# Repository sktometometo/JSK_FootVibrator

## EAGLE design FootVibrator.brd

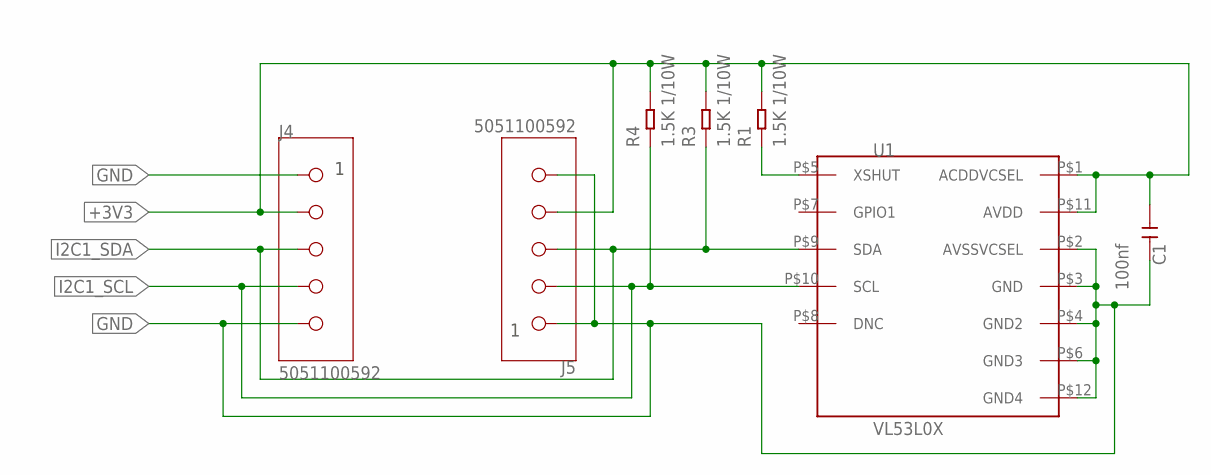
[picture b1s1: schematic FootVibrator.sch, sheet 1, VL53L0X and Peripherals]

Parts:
C1: 100nf; C0603
J4, J5: 5051100592
R1, R3, R4: 1.5K 1/10W; R0603
U1: VL53L0X

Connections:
+3V3: C1.1, J4.2, J5.4, R1.2, R3.2, R4.2, U1.P$1 (ACDDVCSEL), U1.P$11 (AVDD); also elsewhere on the board
GND: C1.2, J4.1, J4.5, J5.1, J5.5, U1.P$2 (AVSSVCSEL), U1.P$3 (GND), U1.P$4 (GND2), U1.P$6 (GND3), U1.P$12 (GND4); also elsewhere on the board
I2C1_SCL: J4.4, J5.2, R4.1, U1.P$10 (SCL); also elsewhere on the board
I2C1_SDA: J4.3, J5.3, R3.1, U1.P$9 (SDA); also elsewhere on the board
VL_XSHUT: R1.1, U1.P$5 (XSHUT)

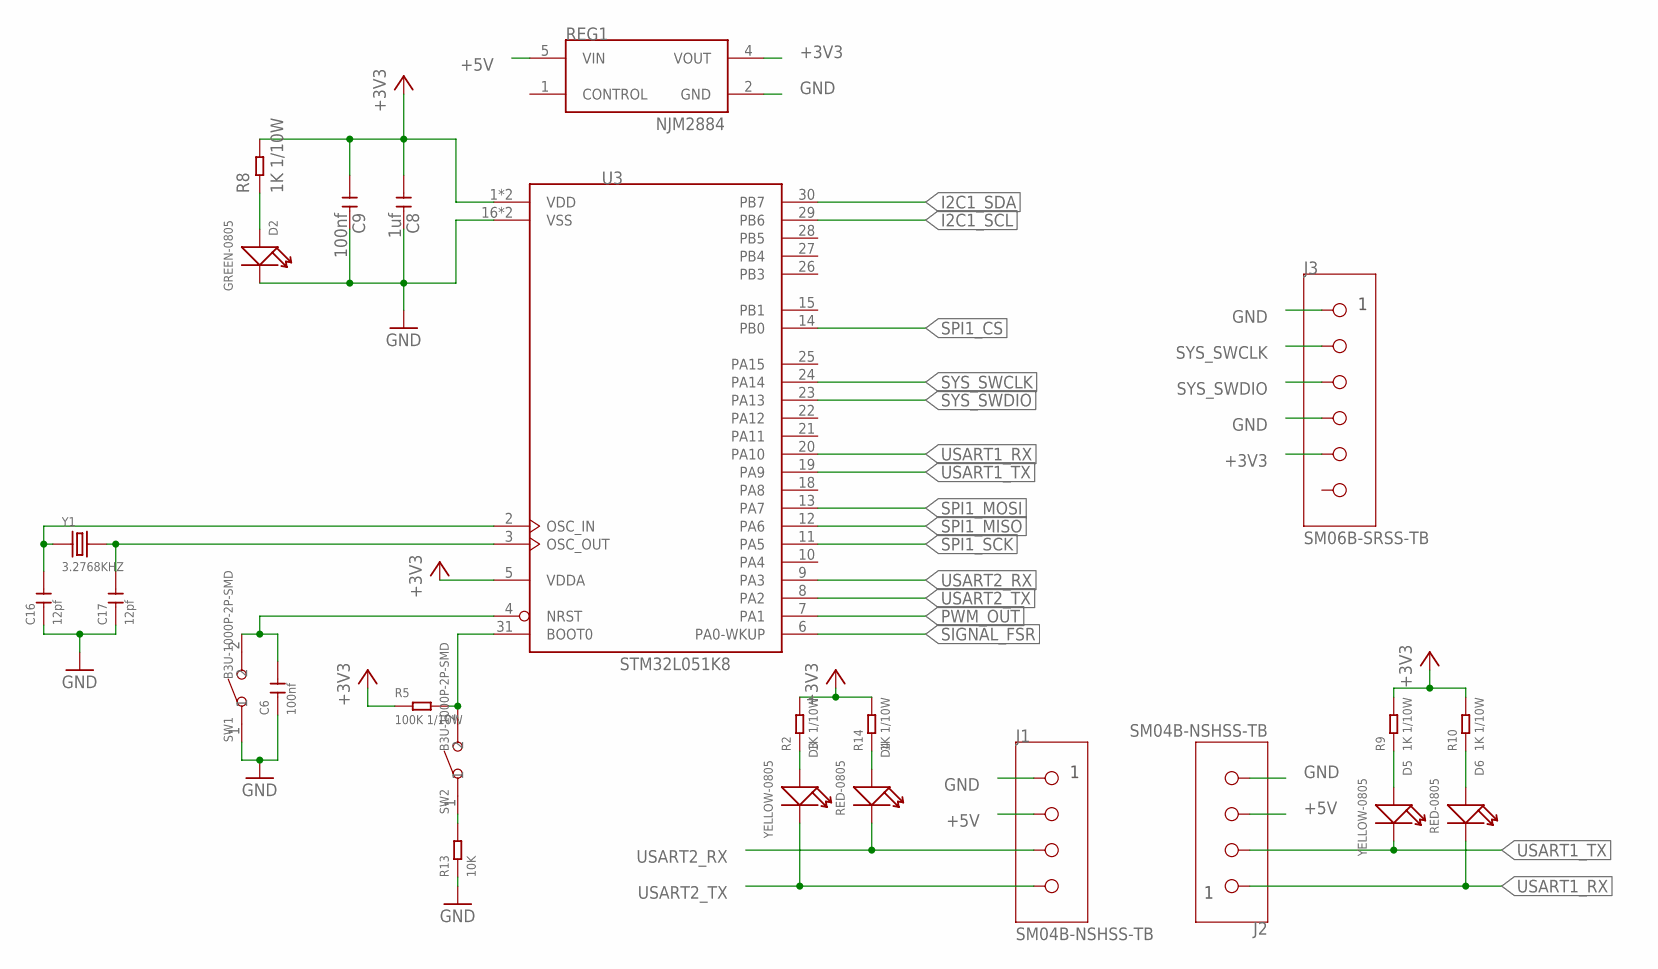
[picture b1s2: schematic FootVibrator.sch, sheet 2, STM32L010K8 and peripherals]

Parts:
C6, C9: 100nf; C0603
C8: 1uf; C0603
C16, C17: 12pf; C0603
D2: GREEN-0805; LED-0805
D3, D5: YELLOW-0805; LED-0805
D4, D6: RED-0805; LED-0805
J1, J2: SM04B-NSHSS-TB
J3: SM06B-SRSS-TB
R2, R8, R9, R10, R14: 1K 1/10W; R0603
R5: 100K 1/10W; R0603
R13: 10K; R0603
REG1: NJM2884; NJM2884-SOT-89-5
SW1, SW2: B3U-1000P-2P-SMD; SW2-2.6-3.0X2.5X1.2+0.4MM
U3: STM32L051K8; LQFP32
Y1: 3.2768KHZ; X2-SMD-L2.0X1.2X0.55MM

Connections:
+3V3: C8.1, C9.1, J3.5, R2.2, R5.1, R8.2, R9.2, R10.2, R14.2, REG1.4 (VOUT), U3.1 (VDD), U3.5 (VDDA), U3.17 (VDD); also elsewhere on the board
+5V: J1.P$2 (2), J2.P$3 (3), REG1.5 (VIN)
GND: C6.1, C8.2, C9.2, C16.1, C17.1, D2.-, J1.P$1 (1), J2.P$4 (4), J3.1, J3.4, R13.1, REG1.2 (GND), SW1.1, U3.16 (VSS), U3.32 (VSS); also elsewhere on the board
I2C1_SCL: U3.29 (PB6); also elsewhere on the board
I2C1_SDA: U3.30 (PB7); also elsewhere on the board
unnamed: R5.2, SW2.2, U3.31 (BOOT0)
unnamed: D3.+, R2.1
unnamed: R13.2, SW2.1
unnamed: D5.+, R9.1
unnamed: D6.+, R10.1
unnamed: D2.+, R8.1
unnamed: C6.2, SW1.2, U3.4 (NRST)
unnamed: D4.+, R14.1
OCC_IN: C16.2, U3.2 (OSC_IN), Y1.1
OCC_OUT: C17.2, U3.3 (OSC_OUT), Y1.2
PWM_OUT: U3.7 (PA1); also elsewhere on the board
SIGNAL_FSR: U3.6 (PA0-WKUP); also elsewhere on the board
SPI1_CS: U3.14 (PB0); also elsewhere on the board
SPI1_MISO: U3.12 (PA6); also elsewhere on the board
SPI1_MOSI: U3.13 (PA7); also elsewhere on the board
SPI1_SCK: U3.11 (PA5); also elsewhere on the board
SYS_SWCLK: J3.2, U3.24 (PA14)
SYS_SWDIO: J3.3, U3.23 (PA13)
USART1_RX: D6.-, J2.P$1 (1), U3.20 (PA10)
USART1_TX: D5.-, J2.P$2 (2), U3.19 (PA9)
USART2_RX: D4.-, J1.P$3 (3), U3.9 (PA3)
USART2_TX: D3.-, J1.P$4 (4), U3.8 (PA2)

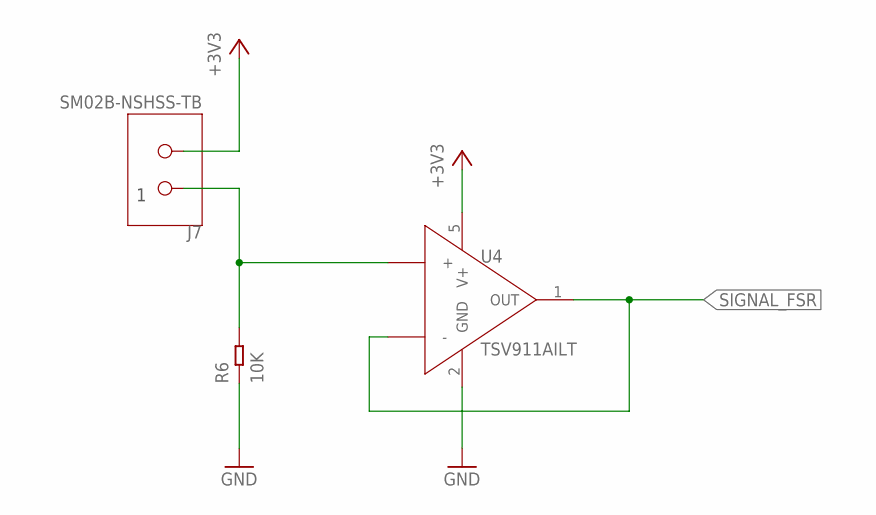
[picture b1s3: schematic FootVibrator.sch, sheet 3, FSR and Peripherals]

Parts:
J7: SM02B-NSHSS-TB
R6: 10K; R0603
U4: TSV911AILT; SOT23-5

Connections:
+3V3: J7.P$2 (2), U4.5 (V+); also elsewhere on the board
GND: R6.1, U4.2 (GND); also elsewhere on the board
RAW_FSR: J7.P$1 (1), R6.2, U4.3 (+)
SIGNAL_FSR: U4.1 (OUT), U4.4 (-); also elsewhere on the board

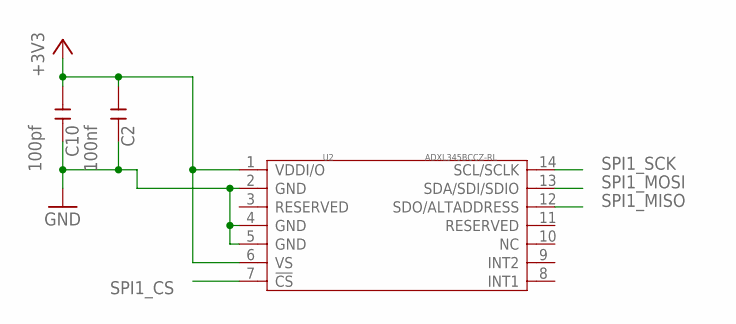
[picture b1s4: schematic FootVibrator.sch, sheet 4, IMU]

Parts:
C2: 100nf; C0603
C10: 100pf; C0603
U2: ADXL345BCCZ-RL; LGA14-0.8-5.0X3.0MM

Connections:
+3V3: C2.1, C10.1, U2.1 (VDDI/O), U2.6 (VS); also elsewhere on the board
GND: C2.2, C10.2, U2.2 (GND), U2.4 (GND), U2.5 (GND); also elsewhere on the board
SPI1_CS: U2.7 (!CS); also elsewhere on the board
SPI1_MISO: U2.12 (SDO/ALTADDRESS); also elsewhere on the board
SPI1_MOSI: U2.13 (SDA/SDI/SDIO); also elsewhere on the board
SPI1_SCK: U2.14 (SCL/SCLK); also elsewhere on the board

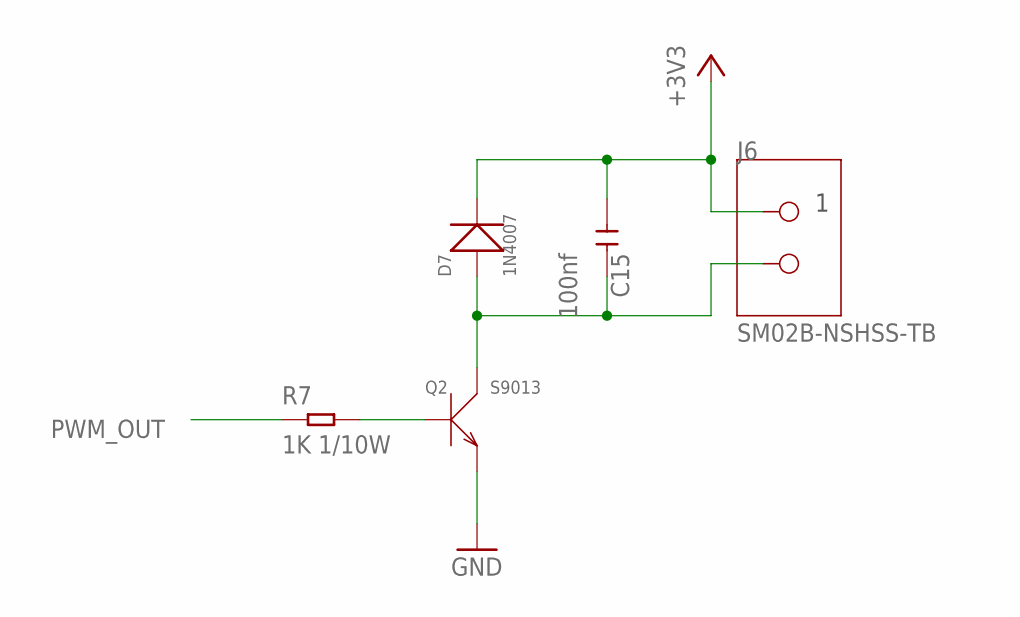
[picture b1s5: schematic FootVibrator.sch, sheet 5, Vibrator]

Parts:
C15: 100nf; C0603
D7: 1N4007; DO-214AC
J6: SM02B-NSHSS-TB
Q2: S9013; SOT-23
R7: 1K 1/10W; R0603

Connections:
+3V3: C15.1, D7.2 (-), J6.P$1 (1); also elsewhere on the board
GND: Q2.2 (E); also elsewhere on the board
unnamed: Q2.1 (B), R7.2
PWM_OUT: R7.1; also elsewhere on the board
RAW_MOTOR: C15.2, D7.1 (+), J6.P$2 (2), Q2.3 (C)

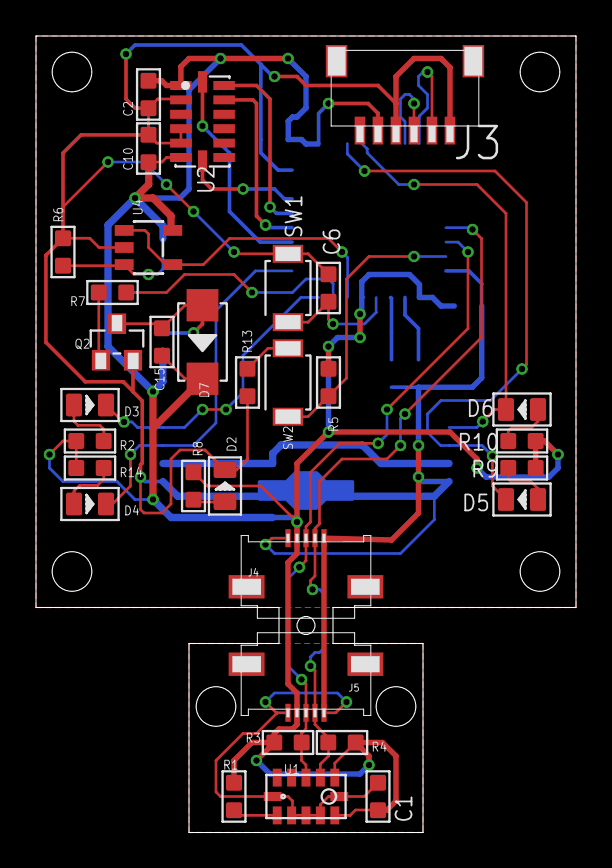
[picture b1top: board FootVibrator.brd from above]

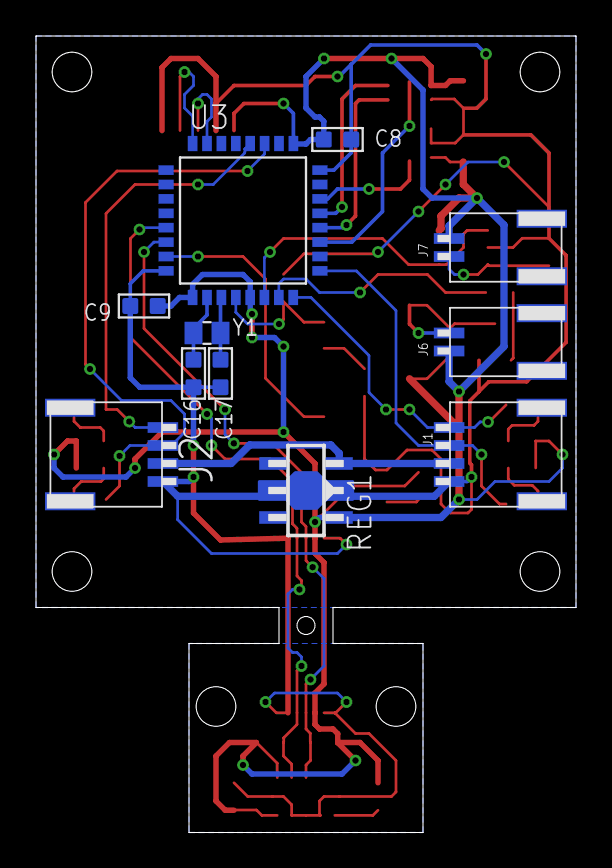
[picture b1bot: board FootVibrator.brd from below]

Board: 2 copper layers, 30.0 x 44.2 mm, 43 parts (11 on the bottom side), 31 nets.

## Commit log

2019-10-22 Initial commit.
2019-10-22 FusionPCB用ガーバーの出力
2019-10-22 4mil版のアートワークの削除
2019-10-22 SeeedOPLを使用するように変更
2019-10-22 コンデンサの数を減らした
2019-10-22 アートワーク引き直した
2019-10-24 ファイルの整理
2019-10-24 タクトスイッチのリンクを修正
2019-10-24 ディレクトリの整理
